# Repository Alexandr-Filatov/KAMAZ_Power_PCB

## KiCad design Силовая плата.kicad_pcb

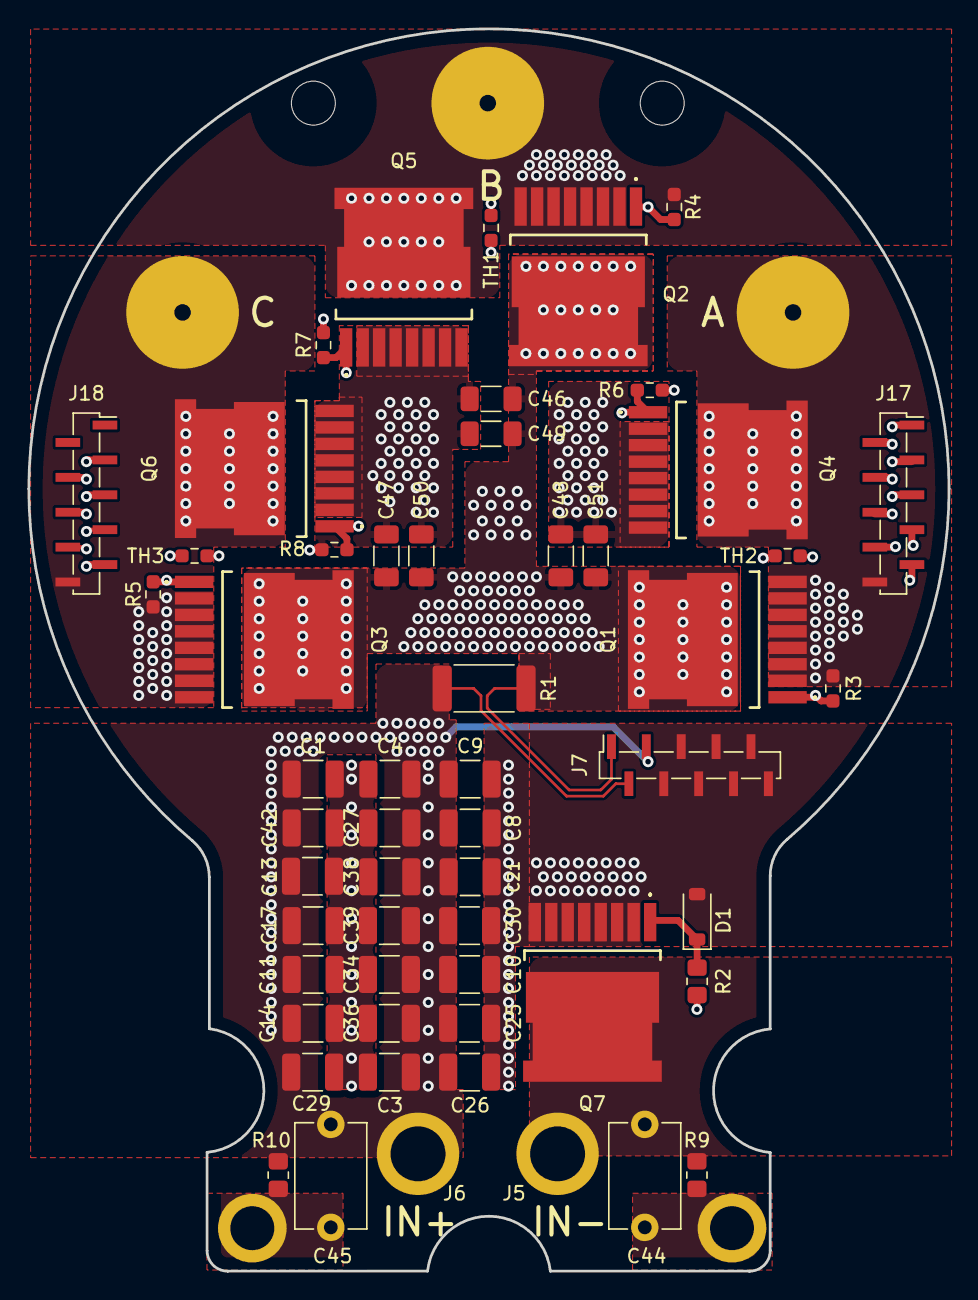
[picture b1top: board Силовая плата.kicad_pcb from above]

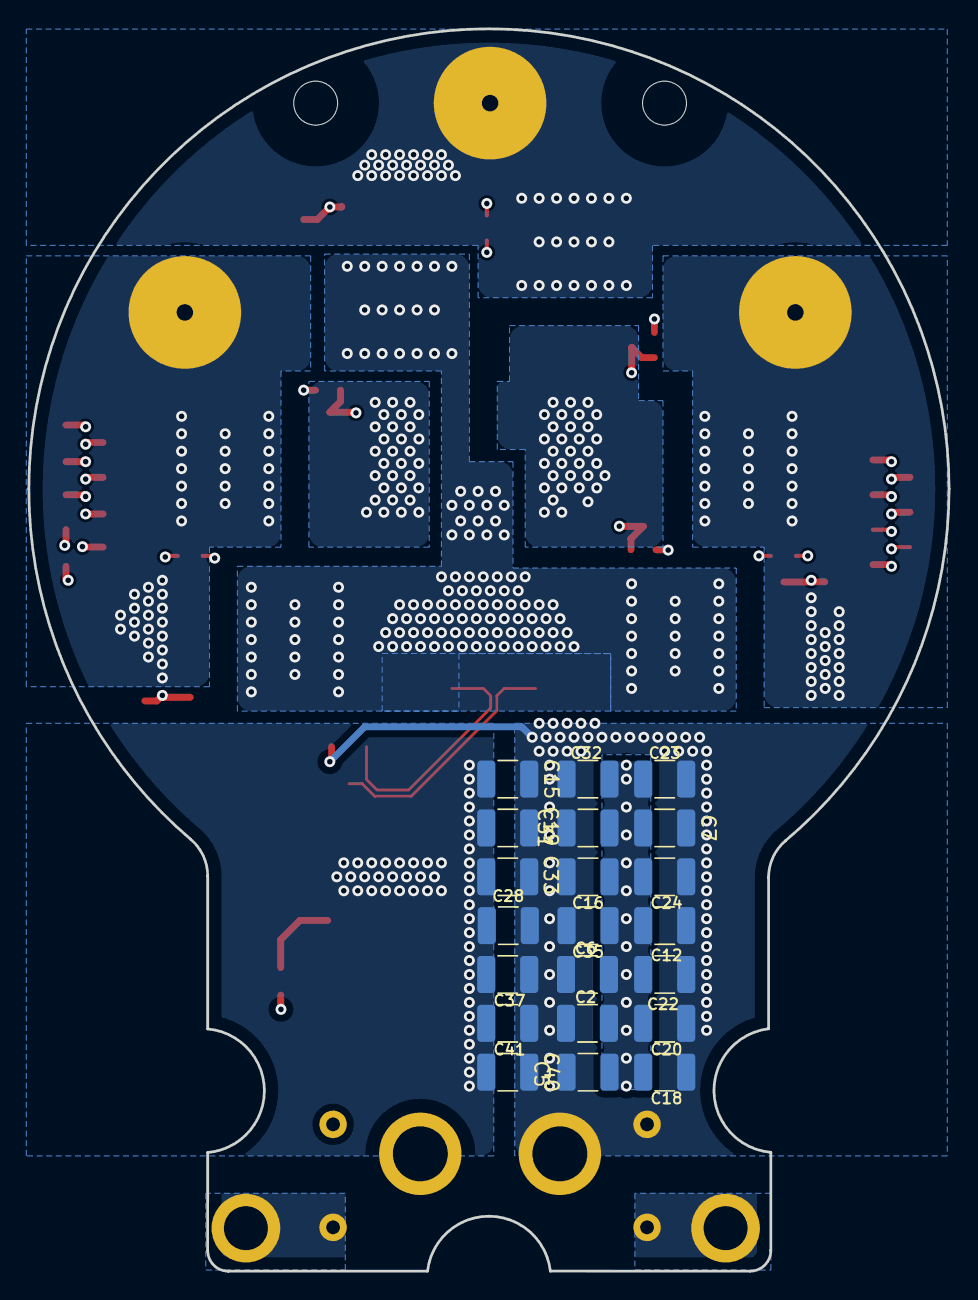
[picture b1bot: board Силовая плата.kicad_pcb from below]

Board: 6 copper layers, 67.0 x 90.5 mm, 83 parts (21 on the bottom side), 21 nets.

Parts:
C1, C2, C3, C4, C5, C6, C7, C8, C9, C10, C11, C12, C13, C14, C15, C16, C17, C18, C19, C20, C21, C22, C23, C24, C25, C26, C27, C28, C29, C30, C31, C32, C33, C34, C35, C36, C37, C38, C39, C40, C41, C42: 10u; C_1210_3225Metric_Pad1.33x2.70mm_HandSolder
C44, C45: 1500p; C_Disc_D7.5mm_W5.0mm_P7.50mm
C46, C47, C48, C49, C50, C51: 10u; C_1206_3216Metric_Pad1.33x1.80mm_HandSolder
D1: BZT52C10; D_SOD-123
H1, H2: MountingHole; MountingHole_3.2mm_M3
J1, J2, J8: A; Power_Wire
J3: B; Power_Wire
J4: C; Power_Wire
J5: IN-; Power_Wire
J6: IN+; Power_Wire
J7, J17, J18: Conn_01x10; PinSocket_1x10_P1.27mm_Vertical_SMD_Pin1Right
Q1, Q2, Q3, Q4, Q5, Q6: 2N7002; IPTG007N06NM5ATMA1
Q7: BSS214NW; IPTG007N06NM5ATMA1
R1: PU2512FKGP60U5L; R_2512_6332Metric_Pad1.40x3.35mm_HandSolder
R2: 100k; R_0805_2012Metric_Pad1.20x1.40mm_HandSolder
R3, R4, R5, R6, R7, R8: 10k; R_0603_1608Metric_Pad0.98x0.95mm_HandSolder
R9, R10: 1M; R_0805_2012Metric_Pad1.20x1.40mm_HandSolder
TH1, TH2, TH3: Thermistor_NTC; R_0603_1608Metric_Pad0.98x0.95mm_HandSolder

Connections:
A: J1.1, J17.10, Q1.2 (S), Q4.3 (D), R3.2
B: J3.1, J17.4, Q2.2 (S), Q5.3 (D), R4.2
C: J4.1, J18.10, Q3.2 (S), Q6.3 (D), R5.2
Earth_Protective: C44.1, C45.2, J2.1, J8.1, R9.2, R10.1
G1: J17.9, Q1.1 (G), R3.1
G2: J17.5, Q4.1 (G), R6.1
G3: J17.3, Q2.1 (G), R4.1
G4: J18.3, Q5.1 (G), R7.1
G5: J18.9, Q3.1 (G), R5.1
G6: J18.5, Q6.1 (G), R8.1
GND: C1.2, C2.2, C3.2, C4.2, C5.2, C6.2, C7.2, C8.2, C9.2, C10.2, C11.2, C12.2, C13.2, C14.2, C15.2, C16.2, C17.2, C18.2, C19.2, C20.2, C21.2, C22.2, C23.2, C24.2, C25.2, C26.2, C27.2, C28.2, C29.2, C30.2, C31.2, C32.2, C33.2, C34.2, C35.2, C36.2, C37.2, C38.2, C39.2, C40.2, C41.2, C42.2, C46.2, C47.2, C48.2, C49.2, C50.2, C51.2, D1.2 (A), J7.4, J7.5, J7.6, J7.7, J7.8, J7.9, J7.10, J17.6, J18.4, J18.6, Q4.2 (S), Q5.2 (S), Q6.2 (S), Q7.2 (S), R6.2, R7.2, R8.2
NTC_A+: J17.7, TH2.1
NTC_A-: J17.8, TH2.2
NTC_B+: J17.2, TH1.1
NTC_B-: J17.1, TH1.2
NTC_C+: J18.7, TH3.1
NTC_C-: J18.8, TH3.2
unnamed: D1.1 (K), Q7.1 (G), R2.1
unnamed: C44.2, J5.1, Q7.3 (D), R9.1
Shunt+: C1.1, C2.1, C3.1, C4.1, C5.1, C6.1, C7.1, C8.1, C9.1, C10.1, C11.1, C12.1, C13.1, C14.1, C15.1, C16.1, C17.1, C18.1, C19.1, C20.1, C21.1, C22.1, C23.1, C24.1, C25.1, C26.1, C27.1, C28.1, C29.1, C30.1, C31.1, C32.1, C33.1, C34.1, C35.1, C36.1, C37.1, C38.1, C39.1, C40.1, C41.1, C42.1, C45.1, J6.1, J7.2, J7.3, R1.1, R2.2, R10.2
Shunt-: C46.1, C47.1, C48.1, C49.1, C50.1, C51.1, J7.1, Q1.3 (D), Q2.3 (D), Q3.3 (D), R1.2

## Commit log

2023-09-14 Первый коммит
2023-09-18 Базовый вариант
2023-09-18 Вариант с транзисторами в линию
2023-09-18 Добавил датчики тока и шунты
2023-10-19 Начальная версия
2023-10-19 Стартовый вариант
2023-10-25 Добавил шунты
2023-10-25 Для презентации
2023-10-30 Добавил выводы под провода
2023-10-30 Стартовая версия
2023-11-08 Добавил температурный контур
2023-11-13 Перенес защиту от переполюсовки и добавил керамику
2023-11-16 Поставил керамические Y конденсаторы
2023-11-26 Изменил контур под новую крышку
2023-11-27 Добавил крепежные отверстия
2023-12-01 Подрезал края платы под новый контур
2023-12-03 Поменял NTC на цифровые датчики
2023-12-12 Фигальная доработка
2023-12-14 Поправил шелкографию
2023-12-17 Добавил документы
2023-12-24 Отчётная версия
2024-05-16 Версия в производство 1.0
2024-05-16 Изменил разъём 2.54мм на 2.0мм
2024-07-22 Не битый репозиторий
2024-07-22 Убрал слабое место полигона +24В
2024-07-26 Добавил снабберы
2024-07-26 Передвинул снабберы
2024-07-26 REV1.2
2024-07-28 Первый вариант
2024-08-01 VER2.0
2024-08-12 Добавил NTC с разъёмом
2024-08-12 Сохранил схему
2024-09-18 Заменил разъёмы 2.54 на 1.27мм
2024-09-25 Добавил подтяжки затворов на плату
2024-09-29 Добавил мегаомные резисторы
2024-09-30 Добавил модель плты
2024-10-01 Добавил все в BOM
2024-10-02 Отправил на проверку в резонит
2024-12-02 Изменения: добавил папку с отчетностью
2024-12-11 Изменения: исправил координаты посадочного места стойки В
